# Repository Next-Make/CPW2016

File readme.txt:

To get temperature in degC, take the value of the binary number on the LED display and divide by 8.
The second to rightmost LED takes the value 1.

<Front Top of PCB>
_________________________________________________________________________
| LED10 | LED9  | LED8 | LED7 | LED6 | LED5 | LED4 | LED3 | LED2 | LED1 |
| = 256 | = 128 | = 64 | = 32 | = 16 | = 8  | = 4  | = 2  | = 1  | N/A  |
‾‾‾‾‾‾‾‾‾‾‾‾‾‾‾‾‾‾‾‾‾‾‾‾‾‾‾‾‾‾‾‾‾‾‾‾‾‾‾‾‾‾‾‾‾‾‾‾‾‾‾‾‾‾‾‾‾‾‾‾‾‾‾‾‾‾‾‾‾‾‾‾‾
<Front Bottom of PCB>

So if LED10 and LED8 are on, the value = 265 + 64, and the temperature = (265 + 64)/8.
Which results in 40degC.

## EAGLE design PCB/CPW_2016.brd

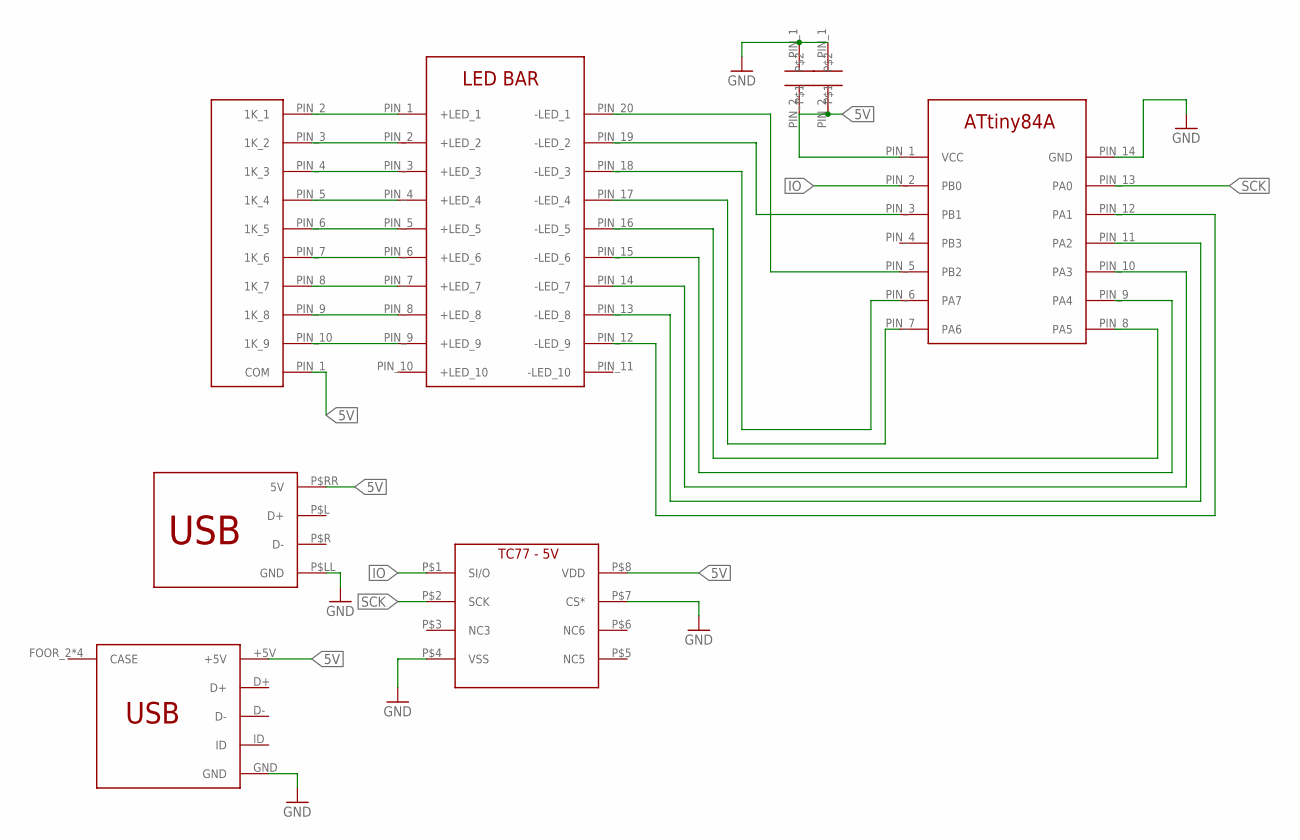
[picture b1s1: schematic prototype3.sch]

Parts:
U$1: 9X_1K_BUSSED_R; SIP-10
U$2, U$6: 10UF_FK18; CAP_FK18
U$3: ATTINY84A; PDIP-14
U$4: LED_X10_BAR
U$5: TC77; SOIC-8
U$7: USB_A_TH
U$8: USB_MINI; SMT_MINI_USB

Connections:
5V: U$1.PIN_1 (COM), U$2.PIN_2, U$3.PIN_1 (VCC), U$5.P$8 (VDD), U$6.PIN_2, U$7.P$RR (5V), U$8.+5V
GND: U$2.PIN_1, U$3.PIN_14 (GND), U$5.P$4 (VSS), U$5.P$7 (CS*), U$6.PIN_1, U$7.P$LL (GND), U$8.GND
IO: U$3.PIN_2 (PB0), U$5.P$1 (SI/O)
unnamed: U$1.PIN_2 (1K_1), U$4.PIN_1 (+LED_1)
unnamed: U$1.PIN_3 (1K_2), U$4.PIN_2 (+LED_2)
unnamed: U$1.PIN_4 (1K_3), U$4.PIN_3 (+LED_3)
unnamed: U$1.PIN_5 (1K_4), U$4.PIN_4 (+LED_4)
unnamed: U$1.PIN_6 (1K_5), U$4.PIN_5 (+LED_5)
unnamed: U$1.PIN_7 (1K_6), U$4.PIN_6 (+LED_6)
unnamed: U$1.PIN_8 (1K_7), U$4.PIN_7 (+LED_7)
unnamed: U$1.PIN_9 (1K_8), U$4.PIN_8 (+LED_8)
unnamed: U$3.PIN_11 (PA2), U$4.PIN_13 (-LED_8)
unnamed: U$3.PIN_12 (PA1), U$4.PIN_12 (-LED_9)
unnamed: U$3.PIN_10 (PA3), U$4.PIN_14 (-LED_7)
unnamed: U$3.PIN_9 (PA4), U$4.PIN_15 (-LED_6)
unnamed: U$3.PIN_8 (PA5), U$4.PIN_16 (-LED_5)
unnamed: U$3.PIN_7 (PA6), U$4.PIN_17 (-LED_4)
unnamed: U$3.PIN_6 (PA7), U$4.PIN_18 (-LED_3)
unnamed: U$3.PIN_3 (PB1), U$4.PIN_19 (-LED_2)
unnamed: U$3.PIN_5 (PB2), U$4.PIN_20 (-LED_1)
unnamed: U$1.PIN_10 (1K_9), U$4.PIN_9 (+LED_9)
SCK: U$3.PIN_13 (PA0), U$5.P$2 (SCK)

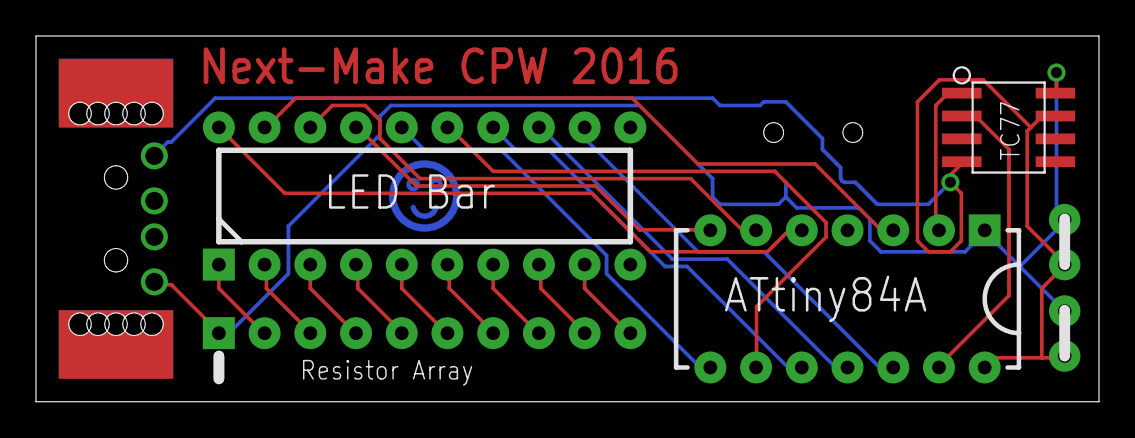
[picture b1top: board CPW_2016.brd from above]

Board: 2 copper layers, 59.1 x 20.3 mm, 8 parts (1 on the bottom side), 22 nets.

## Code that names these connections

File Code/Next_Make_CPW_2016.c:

/*
 * Next_Make_CPW_2015.c
 *
 * Created: 2/28/2015 10:54:56 PM
 * Author: Next-Makers
 */ 


#include <avr/io.h>
#define F_CPU 8000000
#include <util/delay.h>


//PA0 clock line to temp sensor
//PA1 2nd LED
//PA2 3rd LED
//PA3 4th LED
//PA4 5th LED
//PA5 6th LED
//PA6 7th LED
//PA7 8th LED
//PB0 I/O line to temp sensor
//PB1 9th LED
//PB2 10th LED

// num is a number from 0 to 511
void displayAsBinary(int num)
{
	int tempA = PORTA;
	int tempB = PORTB;
	
	tempA = tempA | 0b11111111;
	tempB = tempB | 0b00000110;
	
	if(num >= 256)
	{
		//turn on 10th LED
		tempB &= ~(1 << 2);
		num = num - 256;
	}
	if(num >= 128)
	{
		//turn on 9th LED
		tempB &= ~(1 << 1);
		num = num - 128;
	}
	if(num >= 64)
	{
		//turn on 8th LED
		tempA &= ~(1 << 7);
		num = num - 64;
	}
	if(num >= 32)
	{
		//turn on 7th LED
		tempA &= ~(1 << 6);
		num = num - 32;
	}
	if(num >= 16)
	{
		//turn on 6th LED
		tempA &= ~(1 << 5);
		num = num - 16;
	}
	if(num >= 8)
	{
		//turn on 5th LED
		tempA &= ~(1 << 4);
		num = num - 8;
	}
	if(num >= 4)
	{
		//turn on 4th LED
		tempA &= ~(1 << 3);
		num = num - 4;
	}
	if(num >= 2)
	{
		//turn on 3rd LED
		tempA &= ~(1 << 2);
		num = num - 2;
	}
	if(num >= 1)
	{
		//turn on 2nd LED
		tempA &= ~(1 << 1);
		num = num - 1;
	}
	
	//set to outputs
	PORTA = tempA;
	PORTB = tempB;
}

void runCoolAnimation(void)
{
	int animationVal = 1;

	for(int count = 0; count < 10; count++){
		displayAsBinary(animationVal);
		_delay_ms(50);

		animationVal = animationVal << 1;
	}

	for(int count = 0; count < 10; count++){
		animationVal = animationVal >> 1;

		displayAsBinary(animationVal);
		_delay_ms(50);
	}

	int animationSeries[10] = {0b1000000001, 0b0100000010, 0b0010000100, 0b0001001000, 0b0000110000, 0b0001001000, 0b0010000100, 0b0100000010, 0b1000000001, 0b0000000000};

	for(int seriesIndex = 0; seriesIndex < 10; seriesIndex++){
		displayAsBinary(animationSeries[seriesIndex]);
		_delay_ms(50);
	}
}

int main(void)
{
	// These set whether our pins are input (0) or output (1) for port A and B
	DDRA = 0b11111111;
	DDRB = 0b00000110;
	
	// Divide clock frequency by 128 because ADCs freak out at 8MHz
	ADCSRA |= 0b00000111;
	
	// ADC auto trigger enable
	//ADCSRA |= 1 << ADATE;
	
	// ADC enable
	//ADCSRA |= 1 << ADEN;
		
	// ADC start conversion
	//ADCSRA |= 1 << ADSC;
	
	//set internal 1.1V as ADC reference
	//ADMUX |= 1 << REFS1;
	
	// Our initial temperature output. Stripy!
	float output = 0b1010101010;
	int rawInput = 0;
	
	// TA = ambient temperature in degrees C, which is what we want to display
	float TA;
	
	// display all LEDs to signify start
	displayAsBinary(0b111111111);
	_delay_us(10000);
	
	displayAsBinary(0b000000000);
	_delay_us(10000);

	// cool animation
	//runCoolAnimation();

	//int x = 0;

    while(1)
    {
		// ADCH should grab the temperature
		// Do a moving average because it looks gross otherwise
		//rawInput = ADCL;
		//rawInput = rawInput + (ADCH<<8);
		//output = 0.9 * output + 0.1 * rawInput;
		
		//VOUT = TC*TA + V0C
		// TA = (VOUT - V0C) / TC
		// We also need to convert the output back to a voltage
		//TA = output/1024.0;
		//TA = TA*2.2;
		//TA = TA - 0.4;
		//TA = TA * 51.28;

		//displayAsBinary((int)(TA*10.0));
		
		int input = 0;
		char neg = 0;
		
		//change IO line to read
		DDRB = 0b00000110;
		_delay_us(100);
		
		//clock in data to uC from temp sensor
		for(int a=0; a<16; a++)
		{
			PORTA = PORTA | (0b00000001);
			_delay_us(1000);
			PORTA = PORTA & (0b11111110);
			_delay_us(1000);
			if(a==0)
			{
				neg = (PINB & (1<<0));
			}
			//else if(a==1)
			//{
				//do nothing
			//	;
			//}
			else if(a<10)
			{
				input = input + (1<<(9-a))*(PINB & (1<<0));
			}
			
		}
		if(neg == 1)
		{
			input = 0;
		}
		
		//change IO line to write
		DDRB = 0b00000111;
		_delay_us(100);
		
		//clock out config info
		PORTB = PORTB & 0b11111110;
		
		for(int a=0; a<16; a++)
		{
			PORTA = PORTA | (0b00000001);
			_delay_us(1000);
			PORTA = PORTA & (0b11111110);
			_delay_us(1000);
		}
		
		/*
		x = x + 1;
		if(x>=512)
		{
			x = 0;
		}
		*/
		displayAsBinary(input);
		
		_delay_us(500000);
    }
}

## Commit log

2016-03-23 adding initial things
2016-03-23 initial things
2016-04-11 moved pcb files to folder
2016-04-11 renamed pcb files for real
2016-04-11 added AVR code
2016-04-11 renamed code files
